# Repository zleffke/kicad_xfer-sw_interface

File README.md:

# kicad_xfer-sw_interface
Pulse Latching RF Transfer Switch Interface for VTGS SX-Band System.  
V1, Rev- Designed to Control a Single [Relcomm RTS-TS3AB-I](https://rfrelaystore.com/product/rts-ts3ab-i/) Transfer Switch.  

The VTGS SX-Band System uses four RTS-TS3AB-I transfer switches to set the RF receive path to an X310 USRP with Dual UBX-160s.
Two transfer switches select the receive band for the USRP Band A RX2 port and Band B RX2 port (S or X).
Two transfer switches select the receive polarization for the selected band (RHCP or LHCP).

## [Relcomm RTS-TS3AB-I](https://rfrelaystore.com/product/rts-ts3ab-i/) Transfer Switch Description
See linked product for full datasheet and feature list.  Features listed below are the pertinent features for the control circuit.
- Pulse Latching, short duration pulse on coil sets latched position.
- 28V Coil Voltage, common negative, pulse on positive side of Coil 1 or 2.
- Indicator feedback, 1P2T switch indicates position.

## V1, Rev- Circuit Design Features
This version / revision submitted to osh park for PCB fab on 20220118.
- TTL Level Control from MCU (+5V / +3V3)
- TTL Level Feedback for MCU (+5V / +3V3)
- Optically Isolated Control (ILD207T)
- LED Current Position Indicator (POS1 - RED, POS2 - BLUE)
- LED Set Position Indicator (pulsed, both green)
- Relay Coil Control via dual W6PQL based FET Switch circuits

## Credit where its due:
The transfer switches in this design are controlled by a [High Current DC Switch](https://www.w6pql.com/high_current_solid-state_dc_switch.htm) based on the W6PQL design.  The specific P-Channel MOSFET is modified for smaller form factor and lower current draw.  The DISABLE feature is not needed and not implemented.

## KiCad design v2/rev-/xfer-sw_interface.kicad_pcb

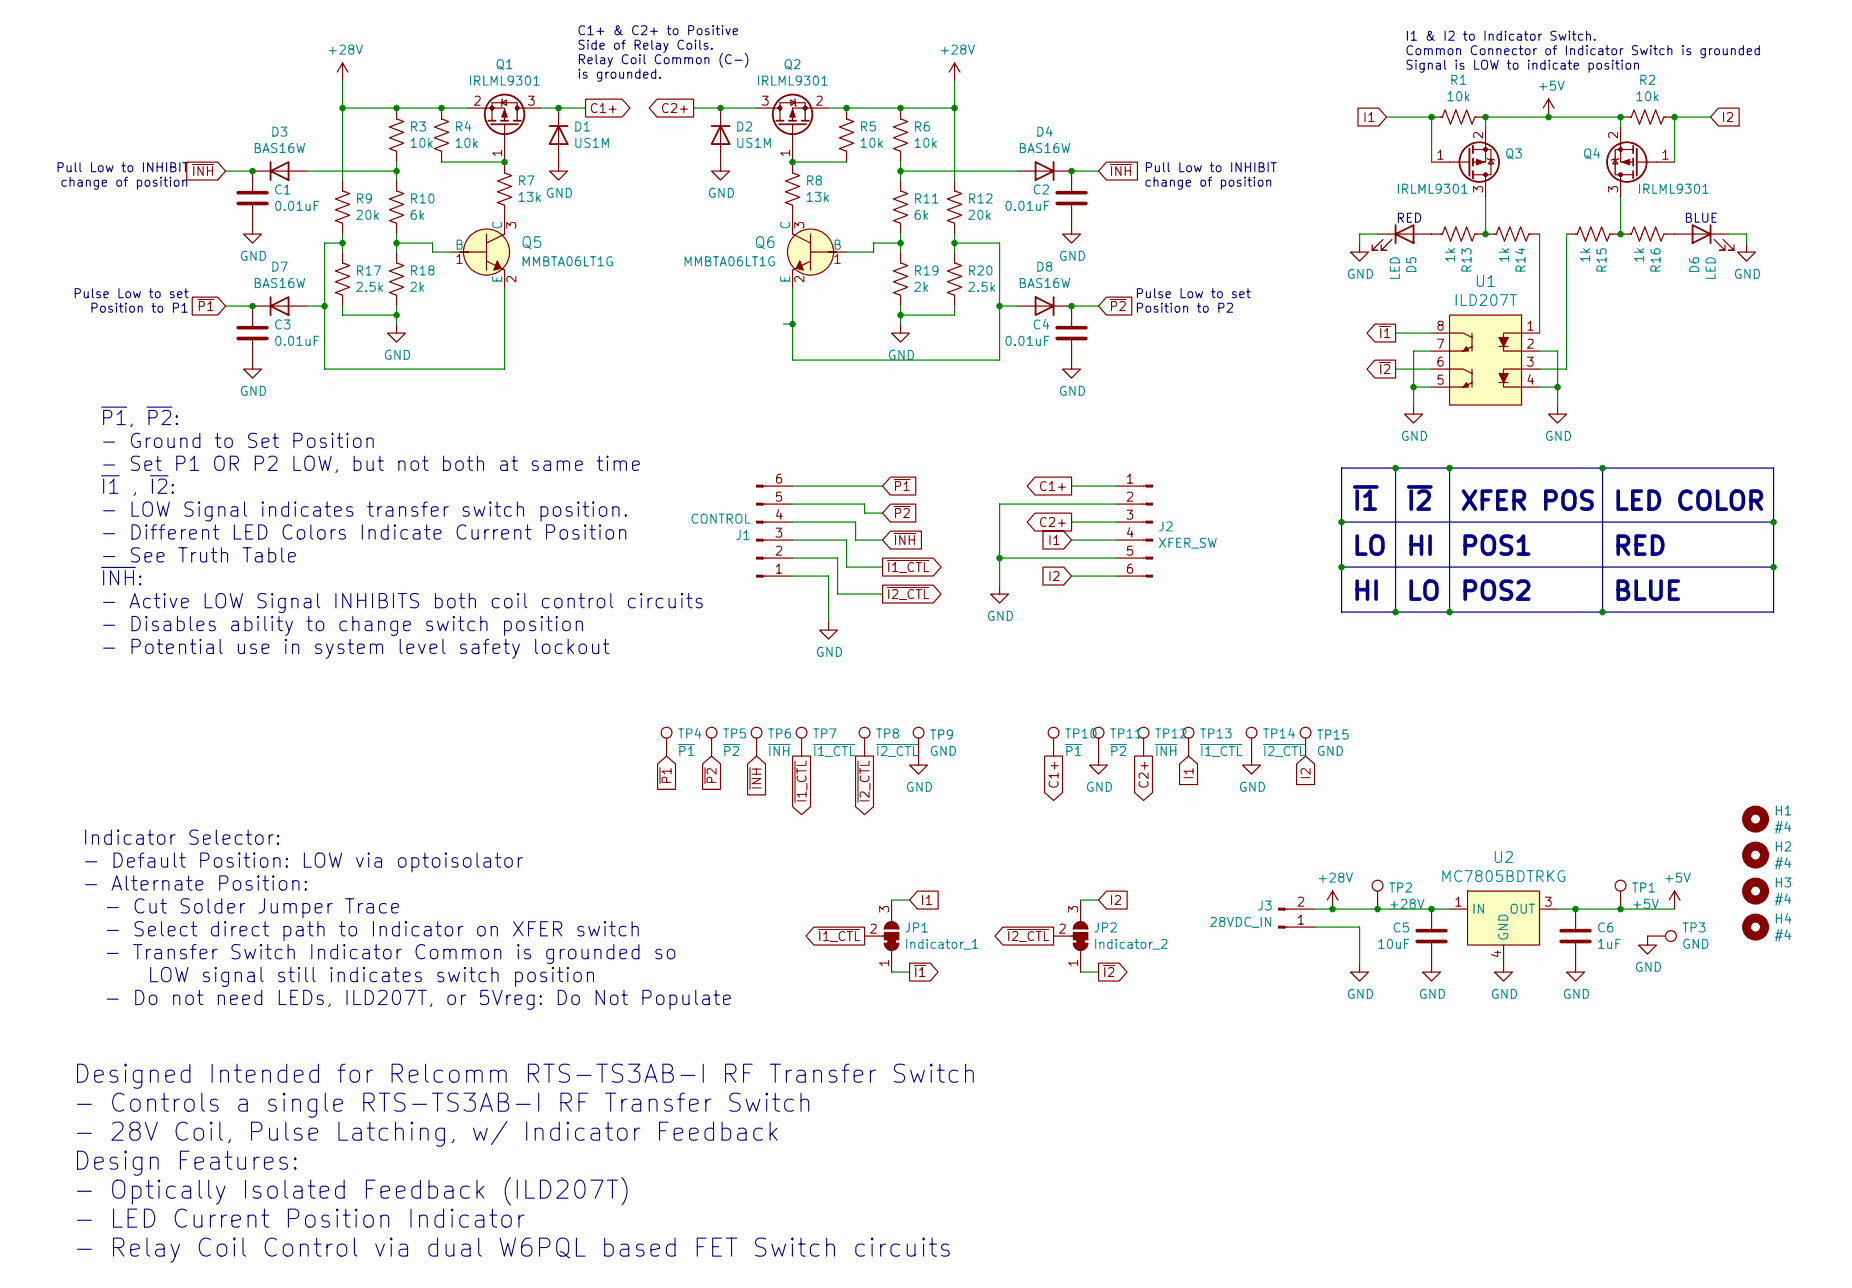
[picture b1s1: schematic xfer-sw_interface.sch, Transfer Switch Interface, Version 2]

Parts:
C1, C2, C3, C4: 0.01uF; 0805
C5: 10uF; 0805
C6: 1uF; 0805
D1, D2: US1M; D_SMA
D3, D4, D7, D8: BAS16W; SOT-23-3
D5, D6: LED; LED_0805_2012Metric
H1, H2, H3, H4: #4; MountingHole_3.2mm_M3
J1: CONTROL; PinHeader_1x06_P2.54mm_Horizontal
J2: XFER_SW; PinHeader_1x06_P2.54mm_Horizontal
J3: 28VDC_IN; PinHeader_1x02_P2.54mm_Vertical
JP1: Indicator_1; SolderJumper-3_P1.3mm_Bridged12_RoundedPad1.0x1.5mm_NumberL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
JP2: Indicator_2; SolderJumper-3_P1.3mm_Bridged12_RoundedPad1.0x1.5mm_NumberL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
Q1, Q2, Q3, Q4: IRLML9301; SOT-23
Q5, Q6: MMBTA06LT1G; SOT-23-3; MPN MMBTA06LT1G; Digi-Key_PN MMBTA06LT1GOSCT-ND
R1, R2, R3, R4, R5, R6: 10k; 0805
R7, R8: 13k; 0805
R9, R12: 20k; 0805
R10, R11: 6k; 0805
R13, R14, R15, R16: 1k; 0805
R17, R20: 2.5k; 0805
R18, R19: 2k; 0805
TP1: +5V; TestPoint_Pad_D1.5mm
TP2: +28V; TestPoint_Pad_D1.5mm
TP3: GND; TestPoint_Pad_D1.5mm
TP4, TP10: ~P1; TestPoint_Pad_2.0x2.0mm
TP5, TP11: ~P2; TestPoint_Pad_2.0x2.0mm
TP6, TP12: ~INH; TestPoint_Pad_2.0x2.0mm
TP7, TP13: ~I1_CTL; TestPoint_Pad_2.0x2.0mm
TP8, TP14: ~I2_CTL; TestPoint_Pad_2.0x2.0mm
TP9, TP15: GND; TestPoint_Pad_2.0x2.0mm
U1: ILD207T; SOIC-8_W3.9mm; MPN ILD207T; Digi-Key_PN 751-1310-1-ND
U2: MC7805BDTRKG; TO-252-3; MPN MC7805BDTRKG; Digi-Key_PN MC7805BDTRKGOSCT-ND

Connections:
+5V: C6.1, Q3.2 (S), Q4.2 (S), R1.1, R2.2, TP1.1, U2.3 (OUT)
+28V: C5.1, J3.2, Q1.2 (S), Q2.2 (S), R3.2, R4.2, R5.2, R6.2, R9.2, R12.2, TP2.1, U2.1 (IN)
C1+: D1.1 (K), J2.1, Q1.3 (D), TP10.1
C2+: D2.1 (K), J2.3, Q2.3 (D), TP12.1
GND: C1.2, C2.2, C3.2, C4.2, C5.2, C6.2, D1.2 (A), D2.2 (A), D5.1 (K), D6.1 (K), J1.1, J2.2, J2.5, J3.1, R17.1, R18.1, R19.1, R20.1, TP3.1, TP9.1, TP11.1, TP14.1, U1.2, U1.4, U1.5, U1.7, U2.4 (GND)
I1: J2.4, JP1.3 (B), Q3.1 (G), R1.2, TP13.1
I2: J2.6, JP2.3 (B), Q4.1 (G), R2.1, TP15.1
unnamed: D3.1 (A), R3.1, R10.2
unnamed: D4.1 (A), R6.1, R11.2
unnamed: D5.2 (A), R13.1
unnamed: D6.2 (A), R16.2
unnamed: D7.1 (A), Q5.2 (E), R9.1, R17.2
unnamed: D8.1 (A), Q6.2 (E), R12.1, R20.2
unnamed: Q1.1 (G), R4.1, R7.1
unnamed: Q2.1 (G), R5.1, R8.1
unnamed: Q3.3 (D), R13.2, R14.1
unnamed: Q4.3 (D), R15.2, R16.1
unnamed: Q5.1 (B), R10.1, R18.2
unnamed: Q5.3 (C), R7.2
unnamed: Q6.1 (B), R11.1, R19.2
unnamed: Q6.3 (C), R8.2
unnamed: R14.2, U1.1
unnamed: R15.1, U1.3
~I1: JP1.1 (A), U1.8
~I1_CTL: J1.3, JP1.2 (C), TP7.1
~I2: JP2.1 (A), U1.6
~I2_CTL: J1.2, JP2.2 (C), TP8.1
~INH: C1.1, C2.1, D3.3 (K), D4.3 (K), J1.4, TP6.1
~P1: C3.1, D7.3 (K), J1.6, TP4.1
~P2: C4.1, D8.3 (K), J1.5, TP5.1

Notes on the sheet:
~P1~, ~P2~: - Ground to Set Position - Set P1 OR P2 LOW, but not both at same time ~I1~ , ~I2~: - LOW Signal indicates transfer switch position. - Different LED Colors Indicate Current Position - See Truth Table ~INH~: - Active LOW Signal INHIBITS both coil control circuits - Disables ability to ch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
~I1
~I2
XFER POS
POS2
POS1
RED
BLUE
LED COLOR
Designed Intended for Relcomm RTS-TS3AB-I RF Transfer Switch - Controls a single RTS-TS3AB-I RF Transfer Switch - 28V Coil, Pulse Latching, w/ Indicator Feedback Design Features: - Optically Isolated Feedback (ILD207T) - LED Current Position Indicator - Relay Coil Control via dual W6PQL based FET S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
Indicator Selector: - Default Position: LOW via optoisolator - Alternate Position: - Cut Solder Jumper Trace - Select direct path to Indicator on XFER switch - Transfer Switch Indicator Common is grounded so LOW signal still indicates switch position - Do not need LEDs, ILD207T, or 5Vreg: Do Not Po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
C1+ & C2+ to Positive Side of Relay Coils. Relay Coil Common (C-) is grounded.
I1 & I2 to Indicator Switch. Common Connector of Indicator Switch is grounded Signal is LOW to indicate position
Pulse Low to set Position to P1
Pull Low to INHIBIT change of position
Pulse Low to set Position to P2

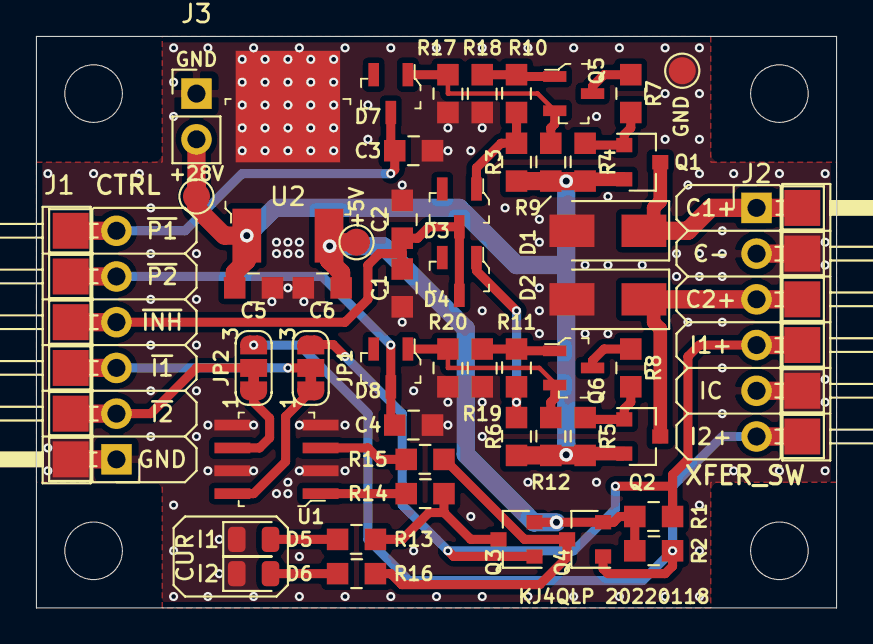
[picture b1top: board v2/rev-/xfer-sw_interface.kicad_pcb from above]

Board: 2 copper layers, 44.4 x 31.8 mm, 66 parts (0 on the bottom side), 30 nets.

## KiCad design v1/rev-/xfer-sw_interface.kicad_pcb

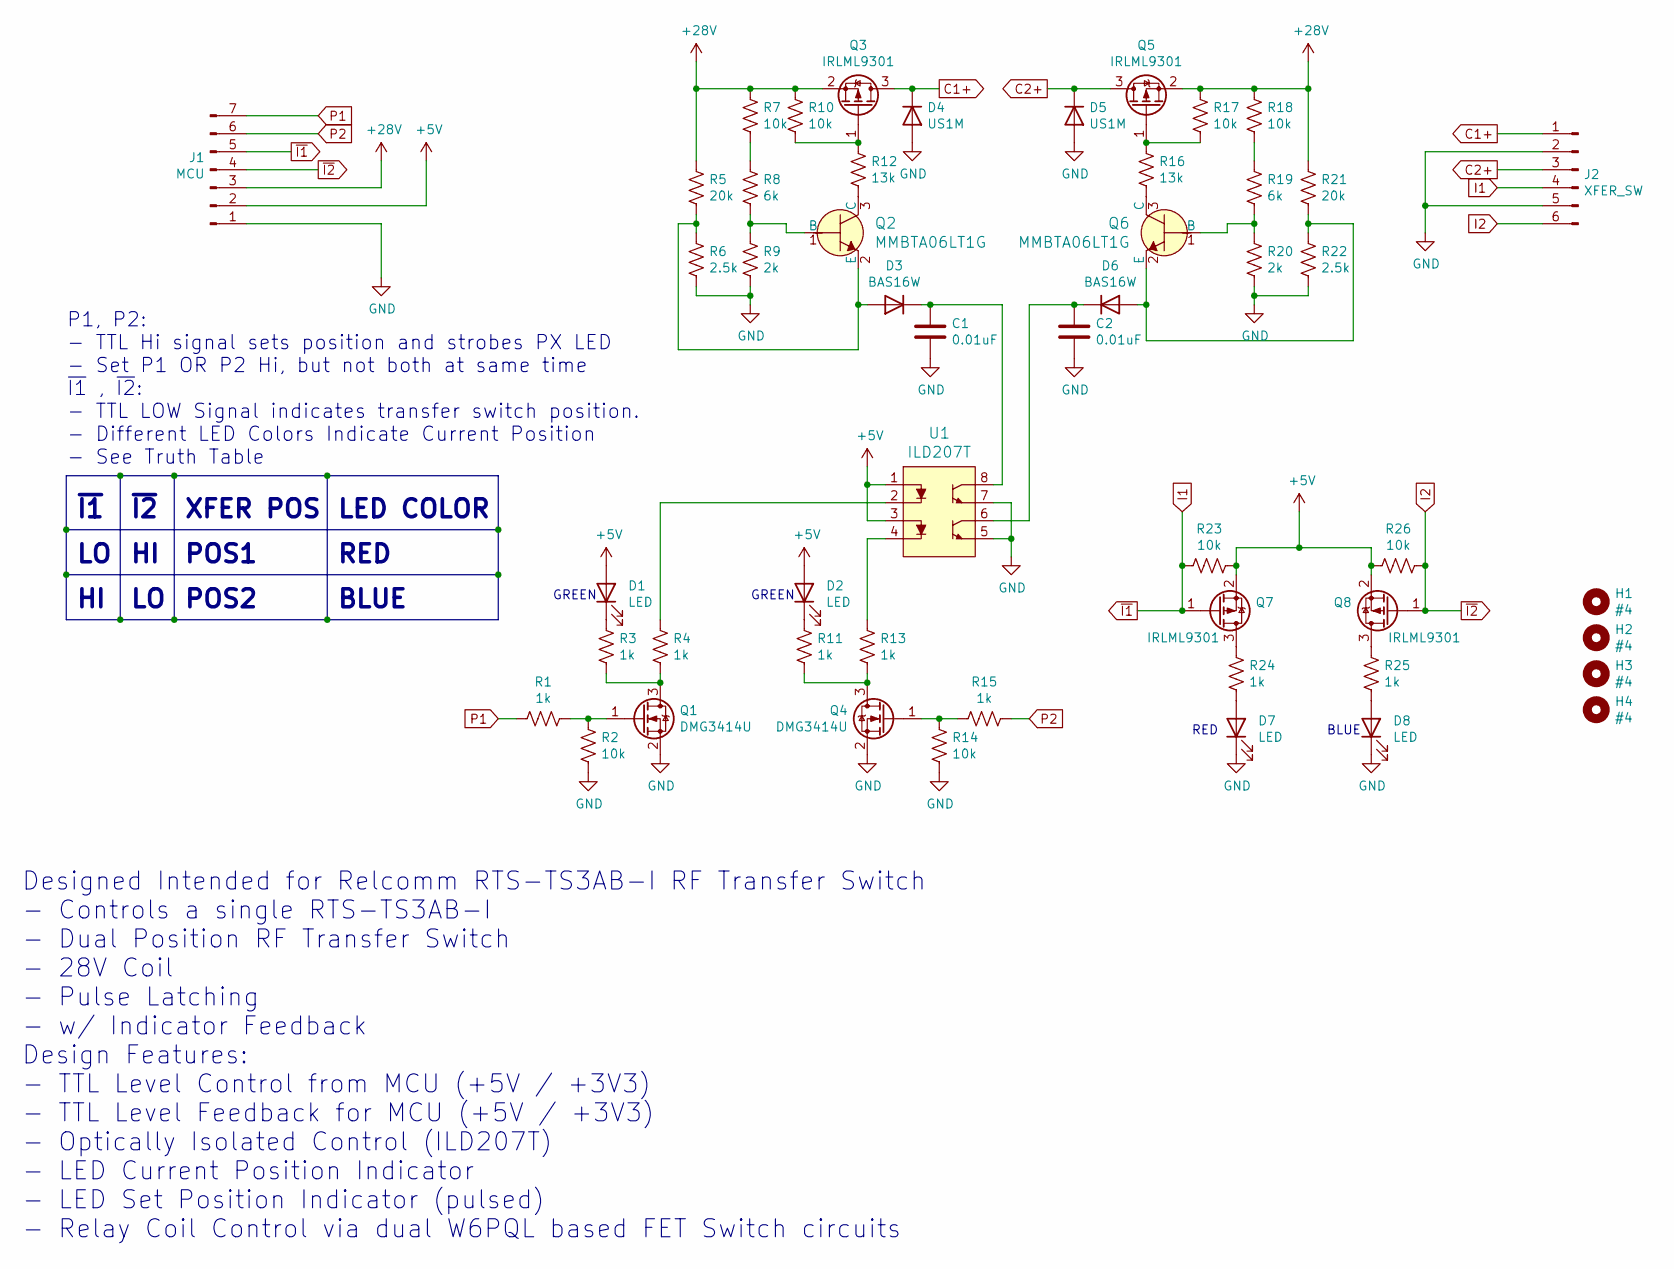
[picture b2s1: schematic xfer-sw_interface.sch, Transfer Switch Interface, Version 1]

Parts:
C1, C2: 0.01uF; 0805
D1, D2, D7, D8: LED; LED_0805_2012Metric
D3, D6: BAS16W; SOT-23-3
D4, D5: US1M; D_SMA
H1, H2, H3, H4: #4; MountingHole_3.2mm_M3
J1: MCU; PinHeader_1x07_P2.54mm_Horizontal
J2: XFER_SW; PinHeader_1x06_P2.54mm_Horizontal
Q1, Q4: DMG3414U; SOT-23
Q2, Q6: MMBTA06LT1G; SOT-23-3; MPN MMBTA06LT1G; Digi-Key_PN MMBTA06LT1GOSCT-ND
Q3, Q5, Q7, Q8: IRLML9301; SOT-23
R1, R3, R4, R11, R13, R15, R24, R25: 1k; 0805
R2, R7, R10, R14, R17, R18, R23, R26: 10k; 0805
R5, R21: 20k; 0805
R6, R22: 2.5k; 0805
R8, R19: 6k; 0805
R9, R20: 2k; 0805
R12, R16: 13k; 0805
U1: ILD207T; SOIC-8_W3.9mm; MPN ILD207T; Digi-Key_PN 751-1310-1-ND

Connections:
+5V: D1.2 (A), D2.2 (A), J1.2, Q7.2 (S), Q8.2 (S), R23.1, R26.2, U1.1, U1.3
+28V: J1.3, Q3.2 (S), Q5.2 (S), R5.2, R7.2, R10.2, R17.2, R18.2, R21.2
C1+: D4.1 (K), J2.1, Q3.3 (D)
C2+: D5.1 (K), J2.3, Q5.3 (D)
GND: C1.2, C2.2, D4.2 (A), D5.2 (A), D7.1 (K), D8.1 (K), J1.1, J2.2, J2.5, Q1.2 (S), Q4.2 (S), R2.1, R6.1, R9.1, R14.1, R20.1, R22.1, U1.5, U1.7
I1: J1.5, J2.4, Q7.1 (G), R23.2
I2: J1.4, J2.6, Q8.1 (G), R26.1
unnamed: C1.1, D3.3 (K), U1.8
unnamed: C2.1, D6.3 (K), U1.6
unnamed: D1.1 (K), R3.2
unnamed: D2.1 (K), R11.2
unnamed: D3.1 (A), Q2.2 (E), R5.1, R6.2
unnamed: D6.1 (A), Q6.2 (E), R21.1, R22.2
unnamed: D7.2 (A), R24.1
unnamed: D8.2 (A), R25.1
unnamed: Q1.1 (G), R1.2, R2.2
unnamed: Q1.3 (D), R3.1, R4.1
unnamed: Q2.1 (B), R8.1, R9.2
unnamed: Q2.3 (C), R12.2
unnamed: Q3.1 (G), R10.1, R12.1
unnamed: Q4.1 (G), R14.2, R15.1
unnamed: Q4.3 (D), R11.1, R13.1
unnamed: Q5.1 (G), R16.1, R17.1
unnamed: Q6.1 (B), R19.1, R20.2
unnamed: Q6.3 (C), R16.2
unnamed: Q7.3 (D), R24.2
unnamed: Q8.3 (D), R25.2
unnamed: R4.2, U1.2
unnamed: R7.1, R8.2
unnamed: R13.2, U1.4
unnamed: R18.1, R19.2
P1: J1.7, R1.1
P2: J1.6, R15.2

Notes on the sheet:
Designed Intended for Relcomm RTS-TS3AB-I RF Transfer Switch - Controls a single RTS-TS3AB-I - Dual Position RF Transfer Switch - 28V Coil - Pulse Latching - w/ Indicator Feedback Design Features: - TTL Level Control from MCU (+5V / +3V3) - TTL Level Feedback for MCU (+5V / +3V3) - Optically Isolat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
P1, P2: - TTL Hi signal sets position and strobes PX LED - Set P1 OR P2 Hi, but not both at same time ~I1~ , ~I2~: - TTL LOW Signal indicates transfer switch position. - Different LED Colors Indicate Current Position - See Truth Table
~I1
~I2
XFER POS
POS2
POS1
RED
GREEN
BLUE
LED COLOR

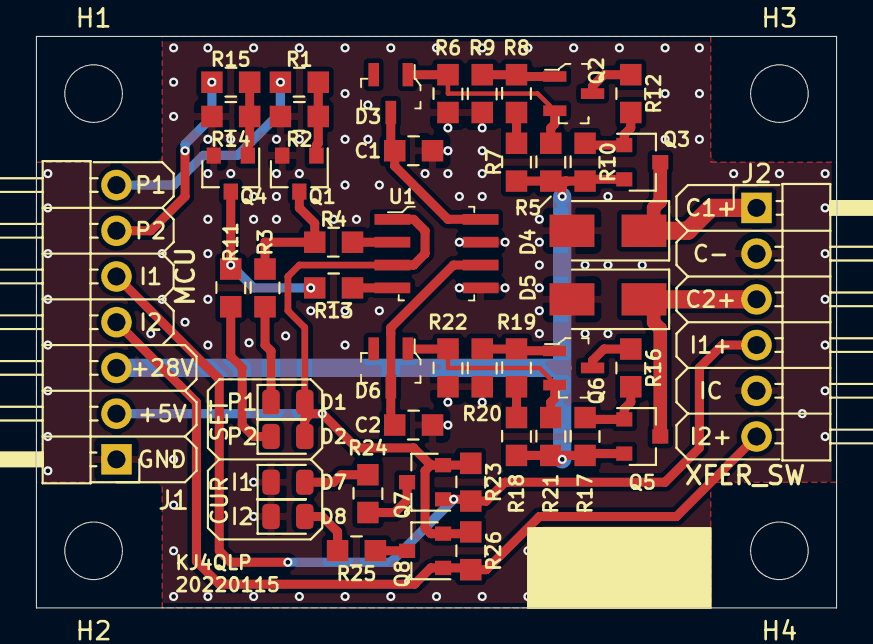
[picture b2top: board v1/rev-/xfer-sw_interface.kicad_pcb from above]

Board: 2 copper layers, 44.4 x 31.8 mm, 51 parts (0 on the bottom side), 33 nets.

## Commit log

2022-01-18 completed v1, rev-. this commit submitted to osh park 20220118.
2022-01-18 initial v2 commit. non-ttl ctrl, opto isolated feedback.
2022-01-19 version 2 of xfer switch interface design. This commit sent to osh park 20220119

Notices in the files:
v1/rev-/xfer-sw_interface.kicad_pcb:
License: CC BY 4.0
v1/rev-/xfer-sw_interface.sch:
creativecommons.org/licenses/by/4.0
